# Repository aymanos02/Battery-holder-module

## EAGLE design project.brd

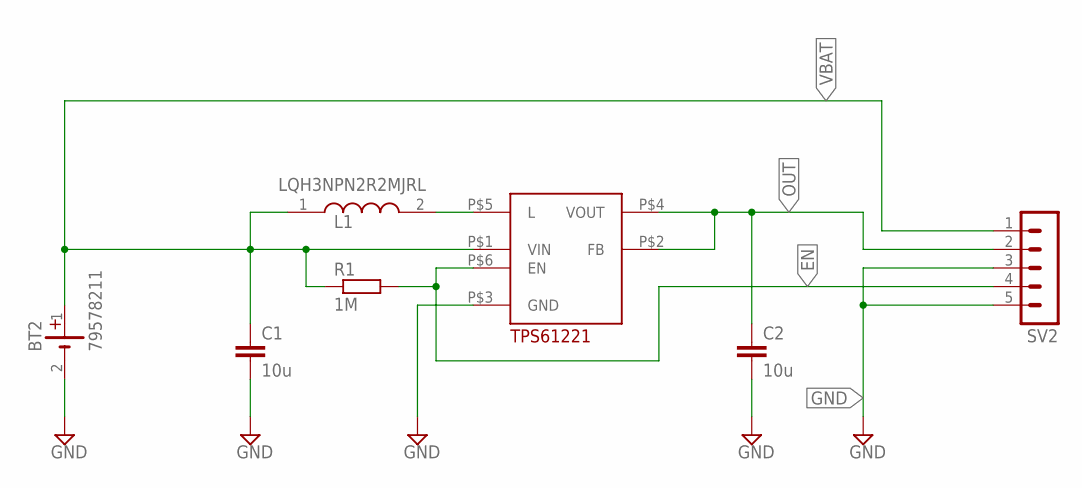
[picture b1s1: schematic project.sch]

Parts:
BT2: 79578211
C1, C2: 10u; C0805K
L1: LQH3NPN2R2MJRL; INDPM3030X120N
R1: 1M; R0805
SV2: MA05-1
U$1: TPS61221

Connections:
EN: R1.2, SV2.4, U$1.P$6 (EN)
GND: BT2.2 (-), C1.2, C2.2, SV2.3, SV2.5, U$1.P$3 (GND)
unnamed: L1.2, U$1.P$5 (L)
OUT: C2.1, SV2.2, U$1.P$2 (FB), U$1.P$4 (VOUT)
VBAT: BT2.1 (+), C1.1, L1.1, R1.1, SV2.1, U$1.P$1 (VIN)

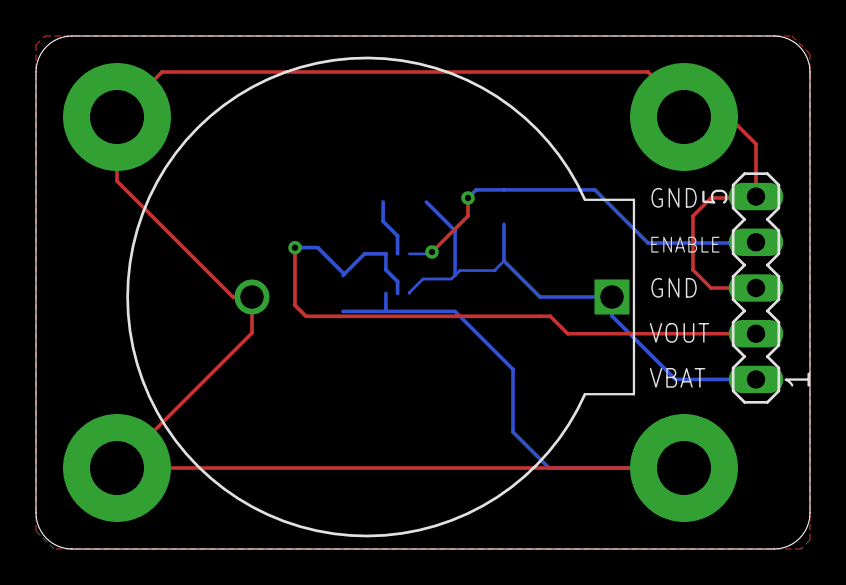
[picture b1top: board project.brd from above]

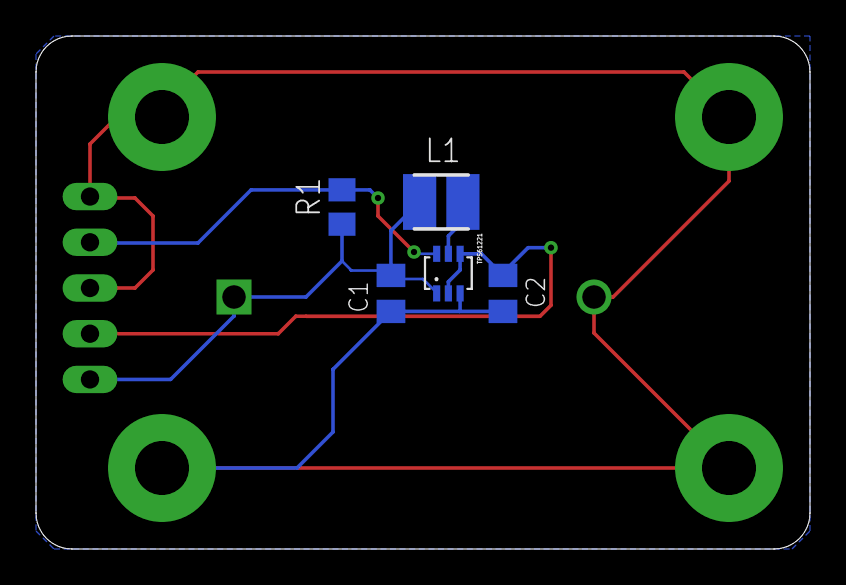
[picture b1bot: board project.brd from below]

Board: 2 copper layers, 43.0 x 28.5 mm, 7 parts (5 on the bottom side), 5 nets.

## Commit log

2020-02-01 the project main
    the project
2020-02-01 the main files
